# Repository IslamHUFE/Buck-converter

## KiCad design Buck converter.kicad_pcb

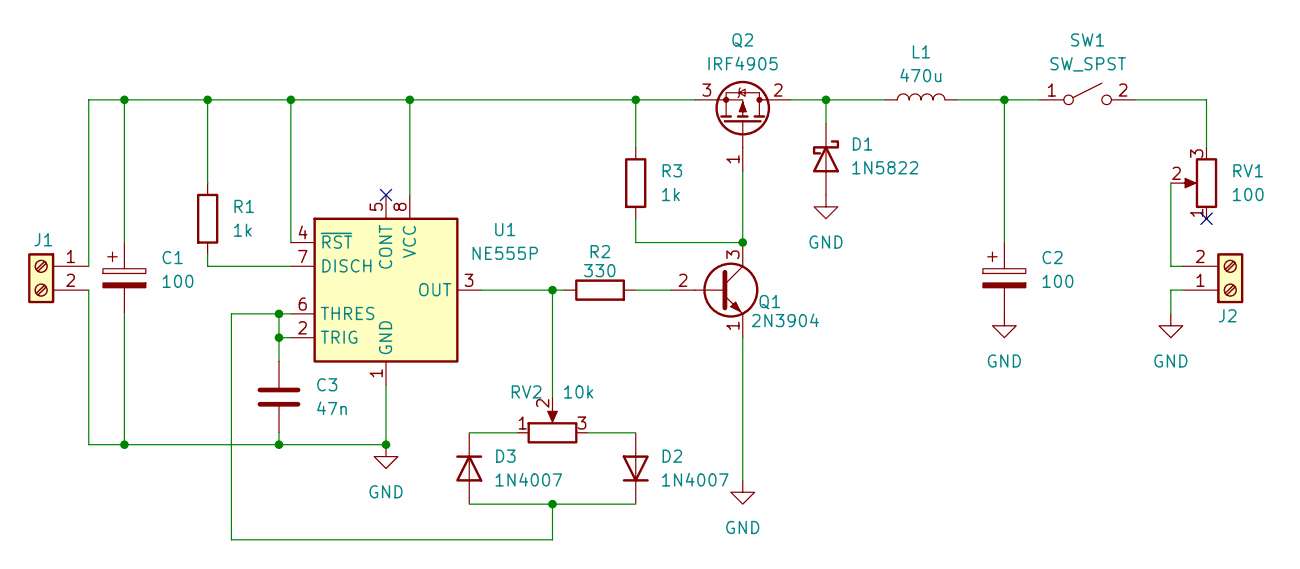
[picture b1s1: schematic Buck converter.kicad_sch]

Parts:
C1, C2: 100; CP_Radial_D8.0mm_P5.00mm
C3: 47n; C_Disc_D4.3mm_W1.9mm_P5.00mm
D1: 1N5822; D_DO-201AD_P15.24mm_Horizontal
D2, D3: 1N4007; D_DO-41_SOD81_P10.16mm_Horizontal
J1, J2: Screw_Terminal_01x02; TerminalBlock_MaiXu_MX126-5.0-02P_1x02_P5.00mm
L1: 470u; L_Axial_L5.3mm_D2.2mm_P10.16mm_Horizontal_Vishay_IM-1
Q1: 2N3904; TO-92_Inline
Q2: IRF4905; TO-220-3_Vertical
R1, R3: 1k; R_Axial_DIN0204_L3.6mm_D1.6mm_P7.62mm_Horizontal
R2: 330; R_Axial_DIN0204_L3.6mm_D1.6mm_P7.62mm_Horizontal
RV1: 100; Potentiometer_Piher_PT-6-V_Vertical
RV2: 10k; Potentiometer_Alps_RK163_Single_Horizontal
SW1: SW_SPST; SW_DIP_SPSTx01_Slide_9.78x4.72mm_W7.62mm_P2.54mm
U1: NE555P; DIP-8_W7.62mm

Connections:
GND: C1.2, C2.2, C3.2, D1.2 (A), J1.2, J2.1, Q1.1 (E), U1.1 (GND)
unnamed: D1.1 (K), L1.1, Q2.2 (D)
unnamed: D2.2 (A), RV2.3
unnamed: C3.1, D2.1 (K), D3.2 (A), U1.2 (TRIG), U1.6 (THRES)
unnamed: D3.1 (K), RV2.1
unnamed: C1.1, J1.1, Q2.3 (S), R1.1, R3.1, U1.4 (~RST), U1.8 (VCC)
unnamed: J2.2, RV1.2
unnamed: Q1.2 (B), R2.2
unnamed: Q1.3 (C), Q2.1 (G), R3.2
unnamed: C2.1, L1.2, SW1.1 (A)
unnamed: RV1.3, SW1.2 (B)
unnamed: R1.2, U1.7 (DISCH)
unnamed: R2.1, RV2.2, U1.3 (OUT)

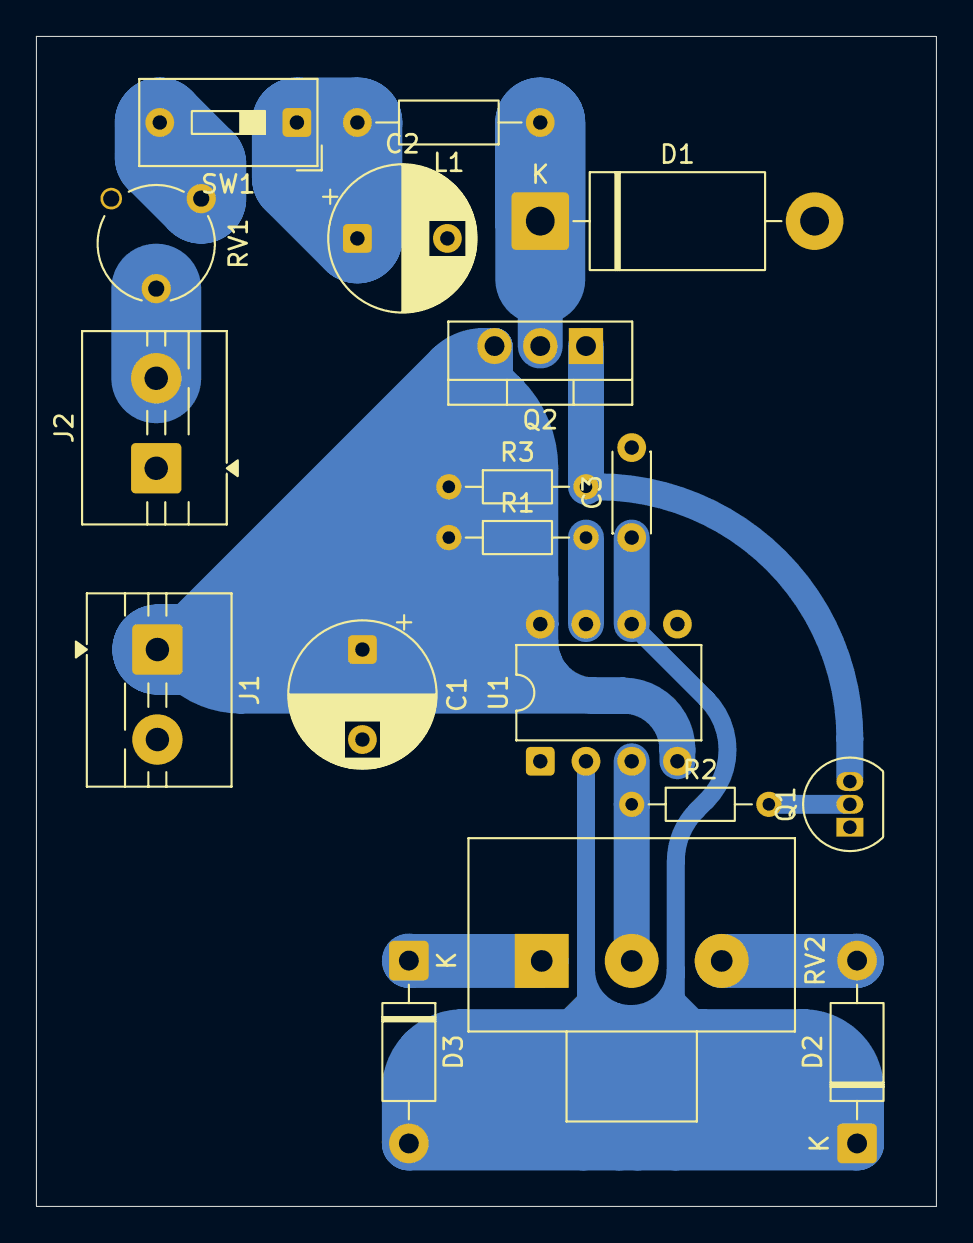
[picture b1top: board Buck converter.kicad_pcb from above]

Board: 2 copper layers, 50.0 x 65.0 mm, 18 parts (0 on the bottom side), 13 nets.

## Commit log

2026-05-14 Intial commit
2026-05-14 LICENCE
2026-05-14 LICENSE
2026-05-14 Add LICENSE file
2026-05-15 bom/
2026-05-15 refresh
2026-05-15 Change artifact upload path for GitHub Pages
